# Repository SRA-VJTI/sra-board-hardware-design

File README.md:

<!-- PROJECT LOGO -->

[![Stargazers][stars-shield]][stars-url]
[![Forks][forks-shield]][forks-url]
[![Issues][issues-shield]][issues-url]
[![License][license-shield]][license-url]

<br/>

<p align="center">

  <h3 align="center">SRA Development Board</h3>
  <p align="center">
    ESP32-based Development Board
    <br />
    <a href="./sra_dev_board_2026">KiCAD</a>
    ·
    <a href="./gerber_sra_dev_board">Gerber</a>
    ·
    <a href="./documentation/images/board_images/front.png">Images</a>
    ·
    <a href="./3d_models/sra_board_model/sra_dev_board_2026.step">3D Model</a>
  </p>

# SRA Board 2026

The SRA board is a development board based on ESP32 with on-board peripherals like a programmable LED matrix, switches, sensor ports for Line Sensor Array and MPU-6050, protection circuit for over-current and reverse voltage, and motor drivers.

## Table of Contents

- [SRA Board 2026](#sra-board-2026)
  - [Table of Contents](#table-of-contents)
  - [Board Images](#board-images)
  - [About the Project](#about-the-project)
  - [Getting Started with a Development Board](#getting-started-with-a-development-board)
  - [Notable problems in the current SRA Board](#notable-problems-in-the-current-sra-board)
  - [Improvements Suggested for Future Iterations](#improvements-suggested-for-future-iterations)
  - [Potential Future Enhancements](#potential-future-enhancements)
  - [3D Models](#3d-models)
  - [Milestones](#milestones)
  - [Contributors](#contributors)
  - [Acknowledgements and Resources](#acknowledgements-and-resources)
  - [License](#license)

## Board Images

- **Frontside**

- **Backside**

## About the Project

- This development board is used for the [Wall-E](https://github.com/SRA-VJTI/Wall-E) and [MARIO](https://github.com/SRA-VJTI/MARIO) workshops conducted by [SRA](https://github.com/SRA-VJTI).
- Designed using KiCAD. The schematic and board files are [here](./sra_dev_board_2026).
- Resources for [previous work](https://github.com/SRA-VJTI/sra-board-hardware-design/tree/v2.5). For more details of the SRA board 2024, checkout this [link](https://github.com/SRA-VJTI/sra-board-hardware-design/releases/tag/v2.4).
- The SRA board 2023 images can be found [here](https://github.com/SRA-VJTI/sra-board-hardware-design/tree/v2.3/documentation/images).
- Older versions of the board and miscellaneous designs can be found [here](https://github.com/SRA-VJTI/PCB-Schematics-and-Layouts).

## Getting Started with a Development Board

In general, every development board has the following basic features:

- ### Power Supply Unit
  - Microcontrollers (MCUs) usually run on 3.3V or 5V logic supply voltage while input to a development board is normally 12V for motor and driving/controlling peripheral devices.
  - So, in order to have a single input source, a _power_ section which inter converts this 12V to standard levels like 5V & 3.3V for MCU and sensors is present.This is achieved using a step-down [buck regulator](https://www.youtube.com/watch?v=m8rK9gU30v4).
  - Buck Regulator IC [MP1584](./datasheets/MP1584_buck.pdf) is used in the current SRA Board 2026 for stepping down the voltage from 12V to 5V DC. This 5V is further regulated to 3.3V using LDO IC [AMS1117-3.3](./datasheets/ams1117_ldo.pdf). The MP1584 is a more compact and efficient alternative compared to the previous LM2576-S.
  - The previous edition of the SRA board (2025) used the [LM2576-S-5](./datasheets/lm2576_buck_regulator.pdf) buck regulator, while earlier editions used the LM7805 linear voltage regulator for stepping down from 12V to 5V.
  - The older editions of the SRA board used the LD33 linear voltage regulator for converting 5V to 3.3V at the sensor port.

- ### Motor Driver
  - Motors usually run on 12V and MCU output is generally 5V/3.3V. So, an external motor driver circuitry is required to control motors according to the MCU input.
  - The current and previous editions of SRA board use the [TB6612FNG](./datasheets/TB6612FNG_motor_driver.pdf) Motor Driver, which is a MOS-based H-Bridge motor driver.
  - The older editions of SRA Board used the L298N IC for motor-control, which is a BJT-based H-Bridge motor driver.

- ### Sensor Port
  - According to the external sensor types, usually development boards have onboard sensor ports where the sensors can be connected easily. [LSA - Line Sensor Array]() and [MPU- Motion Processing Unit]() have on-board connection ports.
  - The current edition uses easily available and efficient [JST XH connectors](https://en.wikipedia.org/wiki/JST_connector).
  - Previous versions used bulky [FRC connectors](<https://www.sunrom.com/c/frc-idc-flat-cable-box-header#:~:text=FRC%20(Flat%20Ribon%20Cable)%20are,from%206%20to%2064%20pins.>)

- ### Protection against [Reverse Voltage](https://www.google.com/url?sa=t&rct=j&q=&esrc=s&source=web&cd=&cad=rja&uact=8&ved=2ahUKEwjc8aaX1c3rAhXXXSsKHXphBgQQFjABegQICxAD&url=https%3A%2F%2Fwww.ti.com%2Flit%2Fpdf%2Fslva139&usg=AOvVaw0Qbub75JJ986MzLv6FYWKE)
  - The SRA Boards use diodes for reverse voltage protection in the power-line.
  - 12V Motor line and power regulated line have been separated with [SS34](./datasheets/ss34_3A_schottky_diode.pdf) and [SS54](./datasheets/ss24_2A_schottky_diode.pdf) schottky diodes respectively.

- ### Protection against [Over Current](https://www.baypower.com/blog/what-is-overcurrent-protection/#:~:text=Overcurrent%20protection%20is%20the%20method,of%20a%20piece%20of%20equipment.)
  - Earlier, for the overcurrent protection of MCU and motor driver circuit, bulky glass fuses of 300mA and 3A were used respectively. After breakdown, they used to be replaced.
  - In the recent versions of the board, these were replaced with compact, PTC Resettable Fuses.
  - On 12V line - [RXEF160](./datasheets/RUEF160_3,2A_trip_ptc_fuse.pdf) : 1.6A hold current; 3.2A trip current Fuse was used.
  - On 5V line - [RXEF160](./datasheets/RXEF050_1A_trip_ptc_fuse.pdf) : 0.5A hold current; 1A trip current Fuse was used.
- ### Programmable Switches and LEDs
  - Every development board should have some programmable switches and LEDs for testing, control and debugging purposes.
  - The current SRA Board 2026 features a 6x5 LED matrix (30 LEDs total) controlled via shift registers, which provides enhanced debugging capabilities and expressive visual feedback while reducing GPIO usage compared to discrete LEDs.
  - The previous edition (2025) had an array of 8 programmable discrete LEDs and switches.
  - The earlier editions had fewer programmable switches and LEDs for testing and control purposes.

- ### Power Switch
  - All versions have a power switch for the motor driver, using which power supply to the motor driver can be toggled. Similarly, there was a switch for the ESP32 MCU.

> Now that we covered basics of development boards, let us talk about the changes made in the new design.

## Changes IN SRA Board Over the years from 2024-2026

|            Feature            |           SRA Board 2024           |           SRA Board 2025           |            SRA Board 2026            |
| :---------------------------: | :--------------------------------: | :--------------------------------: | :----------------------------------: |
|           12V to 5V           |      LM2576-S Buck Converter       |      LM2576-S Buck Converter       |        MP1584 Buck Converter         |
|  Reverse Voltage Protection   |               Diodes               |               Diodes               |                Diodes                |
|   Line Sensing Arrays (LSA)   |             IR Sensors             |             IR Sensors             |              IR Sensors              |
|     Number of LSA Sensors     |                 5                  |                 5                  |                  5                   |
|         Motor Driver          |             TB6612FNG              |             TB6612FNG              |              TB6612FNG               |
|     Stepper Motor Driver      |                 -                  |                 -                  |                  -                   |
|   No. of DC Motor Channels    |                 2                  |                 2                  |                  2                   |
| No. of Stepper Motor Channels |                 0                  |                 0                  |                  0                   |
|        No. of Switches        |                 2                  |                 2                  |                  2                   |
|          No. of LEDs          |                 8                  |                 8                  | 6x5 LED Matrix (via Shift Registers) |
|    Over Current Protection    |        PTC Resettable Fuses        |        PTC Resettable Fuses        |         PTC Resettable Fuses         |
|    Sensor Port Connectors     |           JST Connectors           |           JST Connectors           |            JST Connectors            |
| Component Type and Board Size | SMD(Surface Mount Device), Smaller | SMD(Surface Mount Device), Smaller |  SMD(Surface Mount Device), Smaller  |
|         ESP32 Module          |           Not Integrated           |    Mounted and Soldered to PCB     |     Mounted and Soldered to PCB      |
|         Flashing Port         |             Micro USB              |               Type-C               |                Type-C                |

- ### **Compatiblity of SRA Board with Battery [3- 3.3V 2500mAh Batteries](https://robu.in/product/bak-nmc-18650-2500mah-8c-lithium-ion-battery/?gad_source=1&gclid=Cj0KCQjw6PGxBhCVARIsAIumnWb20iyJUEXE8V6eAfSambP35PfBsSFKje-ALjyNniqGYCW_kz3IbcQaAoeGEALw_wcB)**
  - The SRA Board is compatible with **3-cell (3S) Lithium-ion battery packs** which use an external **[BMS (Battery Management System)](https://robu.in/product/3s-10a-12v-18650-lithium-battery-charger-board-protection-module/)**.
  - The BMS helps maintain safe operating voltages and disconnects the battery when the voltage drops below a safe limit.
  - It also ensures balanced charging and discharging of the three cells, improving the overall health and lifetime of the battery pack.

- ### **7805 (5V linear regulator) to [LM2576/96 Buck Convertor](https://www.youtube.com/watch?v=m8rK9gU30v4)**
  - The higher efficiency, output current capability and reliability of LM2576/96 were the primary reasons for this change.
  - The efficiency of LM2576 can reach up to **~92%**, which is significantly better than the 7805 linear regulator.
  - The LM2576 can provide currents up to **3A**, allowing peripherals such as the MARIO workshop manipulator to be powered using the onboard regulator.

- ### **LD33 (3.3V) to [AMS1117](http://www.advanced-monolithic.com/pdf/ams1117.pdf)**:
  - Older editions used the **LD33 IC** to step down from 5V to 3.3V.
  - This was later replaced with the **AMS1117-3.3 LDO**, which is more compact and widely used for stable 3.3V regulation.
  - (_AMS1117 is also used on the ESP32-DevKitC V4 module._)

- ### **Reverse voltage protection: Diodes to P-MOSFET**
  - Diodes placed in series with the power line introduce voltage drop and power loss compared to a **P-MOSFET based protection circuit**.
  - Due to the higher current requirements of the motors, managing diode size and current rating became difficult.
  - Therefore, earlier versions used a **P-MOSFET based reverse polarity protection circuit**, which is more efficient and can handle higher currents.
  - In the current edition, **SMD Schottky diodes** are used, making size and rating less of an issue.

- ### **Component Type and Board Size**:
  - In the previous editions, THT/PTH (Through-Hole) components were used, which occupied more board area and increased in size with higher power ratings.
  - In the current edition, the design adopts a more compact SMD-based layout. The LM2576 buck converter has been replaced with the smaller MP1584 regulator, and the discrete LED array has been replaced with a 6×5 LED matrix driven using shift registers.
  - Current Board Dimensions: **90mm x 90mm**

- ### **L298N vs [TB6612FNG](https://dronebotworkshop.com/tb6612fng-h-bridge/)**
  - L298N is a BJT-based H-bridge motor driver but it is less efficient as compared to the new MOS-based TB6612FNG.
  - The detailed comparison is shown below. As you can see the efficiency of TB6612FNG can reach up to 91-95% which is significantly higher than the 40-70% efficiency of L298N.
  - The only drawback of TB6612FNG is the less continuous current which is equal to 1.2A.

- ### **LED System**

  - Earlier versions of the board used a set of discrete programmable LEDs for debugging and status indication. In the SRA Board 2026, this has been replaced with a **6×5 LED matrix driven using shift registers**.  
  - This significantly reduces GPIO usage while allowing more flexible visual debugging and status indication patterns.

## Notable problems in the current SRA Board

- ### **Buck Converter Stability Issue (MP1584)**
  - The SRA Board 2026 uses the **MP1584 buck converter** to step down 12V to 5V.
  - While the device allowed a significant reduction in the power section size compared to LM2576, irregular behaviour was observed under **higher load conditions**.
  - During heavy load scenarios involving motors and other peripherals, the **5V rail occasionally showed instability**, which may affect the overall system reliability.

- ### **USB Type-C Connector Mechanical Strength Issue**
  - The board currently uses a **16-pin USB Type-C connector** for programming and power.
  - In practical usage, the connector was found to be **mechanically weak**, and in some cases it could loosen or detach from the PCB after repeated cable insertion or mechanical stress.

- ### **Power Switch Issue**
  - There are two dpdt power toggle switch used on board. One to toggle the supply of 12v to the whole board and one to toggle the supply of 5v to the logic circuit.
  - Instead it should have been toggling 12v supply to the motors and toggling 12v supply to the whole board.

## Improvements Suggested for Future Iterations

Based on the current design of the SRA Board 2026, the following improvements are recommended for future iterations:

- **Replace MP1584 with TPS562202**: The TPS562202 offers improved reliability and enhanced long-term robustness compared to the current MP1584 buck converter. This component provides better thermal performance and more stable regulation across varying load conditions.

- **Upgrade to USB-C 6P Connector**: Replace the current Type-C connector with a robust USB-C 6P connector configuration. This simplifies soldering procedures, improves mechanical strength, and enhances durability during repeated connection cycles.

- **Add Unconnected UART Solder Pads (RX, TX)**: Incorporate unconnected solder pads for UART receive and transmit lines on the PCB. This allows the board to optionally function as a USB-to-TTL interface, extending its utility beyond standalone development applications.

## Potential Future Enhancements

The following experimental features and enhancements are being considered for future versions of the SRA Board but are not yet integrated into the 2026 iteration:

- **Onboard IMU Integration**: Direct integration of an Inertial Measurement Unit (IMU) for advanced motion sensing applications, eliminating the need for external MPU6050 connections.

- **Camera FFC/FPC Connector**: Addition of a Flat Flex Cable (FFC) or Flexible Printed Circuit (FPC) connector to support camera modules, enabling vision-based robotics projects and computer vision applications.

- **Integrated Motor Driver**: Direct onboarding of motor driver circuits instead of requiring external TB6612FNG modules, reducing component count and improving form factor.

- **CH340 to CP2102 Upgrade**: Replacing the CH340 USB-to-UART bridge with CP2102 for improved reliability, driver support across multiple operating systems, and better stability in industrial environments.

These enhancements represent opportunities for evolution of the platform and will be explored as future iterations of the board are developed.

## 3D Models

1. The complete 3D model (.step) file of [SRA Board 2026](./3d_models/sra_board_model/sra_dev_board_2026.step)
2. The 3D models of motor driver, LEDs, ESP32 etc.: [3d models of other components](./3d_models/)

<!-- Milestone -->

## Milestones

- [x] Designing of the prototype board
- [x] Modular testing of the circuit
- [x] Testing of prototype board
- [x] Final version
- [x] Making the board Battery Compatible
- [x] Onboard ESP32 Module

<!-- CONTRIBUTORS -->

## Contributors

- [Vishal Mutha](https://github.com/Vishal-Mutha): _Designer_
- [Atharva Atre](https://github.com/AtharvaAtre): _Mentor_
<!-- ACKNOWLEDGEMENTS AND REFERENCES -->

## Acknowledgements and Resources

- Previous Edition: [SRA Board 2025](https://github.com/SRA-VJTI/sra-board-hardware-design/releases/tag/v2.5)
- [KiCAD Tutorials](https://www.youtube.com/playlist?list=PL3bNyZYHcRSUhUXUt51W6nKvxx2ORvUQB)
- [README Template](https://github.com/roshanlam/ReadMeTemplate) by [roshanlam](https://github.com/roshanlam)

## License

- Distributed under the [MIT License](https://github.com/SRA-VJTI/sraboard-hardware-design/blob/master/LICENSE).

[forks-shield]: https://img.shields.io/github/forks/SRA-VJTI/sra-board-hardware-design
[forks-url]: https://github.com/SRA-VJTI/sra-board-hardware-design/network/members
[stars-shield]: https://img.shields.io/github/stars/SRA-VJTI/sra-board-hardware-design
[stars-url]: https://github.com/SRA-VJTI/sra-board-hardware-design/stargazers
[issues-shield]: https://img.shields.io/github/issues/SRA-VJTI/sra-board-hardware-design
[issues-url]: https://github.com/SRA-VJTI/sra-board-hardware-design/issues
[license-shield]: https://img.shields.io/github/license/SRA-VJTI/sra-board-hardware-design
[license-url]: https://github.com/SRA-VJTI/sra-board-hardware-design/blob/master/LICENSE

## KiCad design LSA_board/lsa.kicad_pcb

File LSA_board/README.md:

## LSA - Line Sensor Array

### Table of Contents
* [Overview](#overview)
* [Features](#features)
* [Components of LSA](#components-of-lsa)
* [Function of Components](#function-of-components)
	* [LED](#function-of-components)
	* [PhotoDiode](#function-of-components)
	* [IC LM324](#function-of-components)
	* [Resistors](#function-of-components)
* [Connections](#connections)
* [Working Principle](#working-principle)
* [Appplications](#applications)
* [Scope of Improvement](#scope-of-improvement)

### Overview
- The Line Sensor Array(LSA) is used to detect the white/black lined surface and it sends this data to the microcontroller ESP-32. Analyzing and processing the data received by the microcontroller ESP-32, the purpose of line following is achieved.

- Physical PCB

- PCB Backside

### Features
* Components used are readily available.
* Easy connections for output signals.
* Compact enough to fit into any project.
* Distinguished trace widths for Signal and Power Routes.

### Components of LSA
| Component   | Description   | Quantity |
| ----------- | ------------- | -------- |
| Infrared Emmitter         | Emits infrared light   |  5       |
| PhotoTransistor  | Absorbs light |  5       |
| Resistors   | Limit Current |  10      |
|JST Connector | Connect PCB with other circuits|1|

### Function of Components
- **Infrared Emmitter**
	- The specific Infrared Emmitter emit infrared light which is incident on the surface and some of it is absorbed by the surface. The voltage source for the Infrared Emmitter to emit is VCC.

- **PhotoTransistor**
	- Based upon the reflectivity coefficient of the surface( generally less than 1), the remaining light reflected from the surface is captured by the Photodiodes. Infrared Emmitter and complimentary phototransistor are used to efficiently detect the surface (white/black line). The amount of light received is directly proportional to the current generated by it. More the light, more the current, more the reading.

- **Resistors**
	- Now to limit the current and thus to protect the LEDs, PhotoDiodes current limiting resistors are used.

### Connections
To connect LSA with the SRA Board, connect the JST connector in the following way:

### Working Principle
- LSA works on the principle of reflectivity of light for different types of surfaces.
	- Black Surface -> HIGH absorptivity -> LESS reflectivity
	- White Surface -> LOW absorptivity -> HIGH reflectivity
- Demonstration

### Applications
* Obstacle detection on a clear path.
* Line Following.
* Distinguish Colours on a path.

### Scope of Improvement
- LSA sometimes provides slightly inaccurate readings due to external light and conditions due to non uniformity of the colour of the path. Therefore, LSA has low accuracy. Hence LSA should be kept close to the ground.
- As of now only white and black surfaces are being mapped. Given accurate sensors and proper mapping we can map LSA for any range of RGB colours.

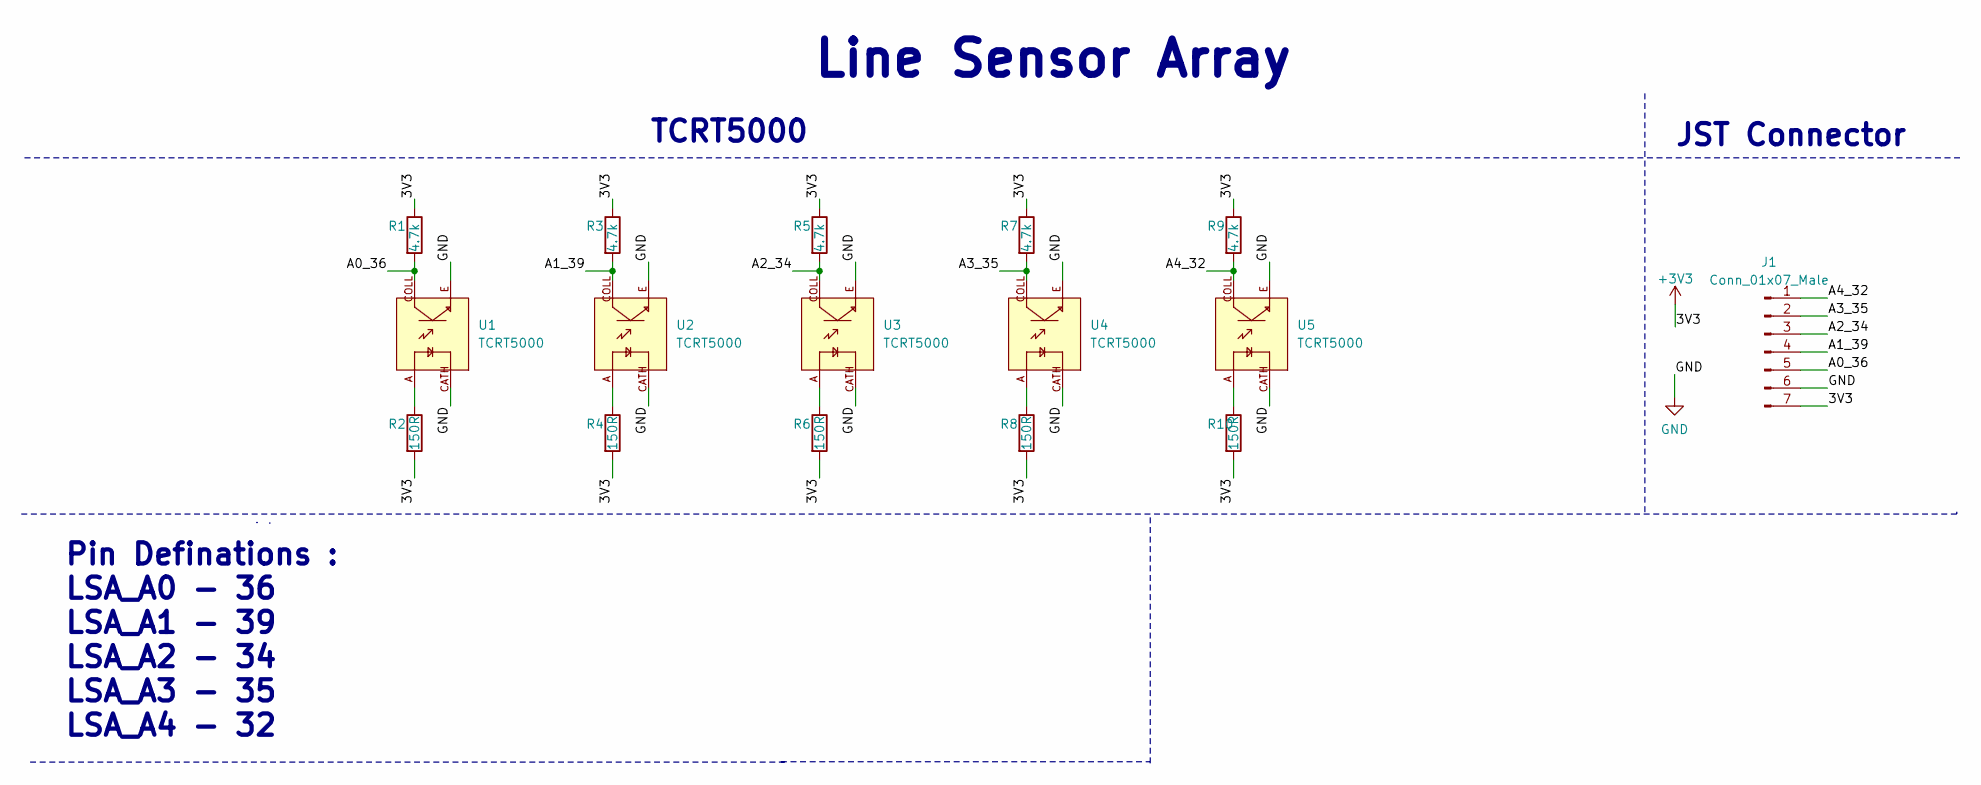
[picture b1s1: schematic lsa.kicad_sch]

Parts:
J1: Conn_01x07_Male; PinHeader_1x07_P2.54mm_Vertical
R1, R3, R5, R7, R9: 4.7k; R_1206_3216Metric_Pad1.30x1.75mm_HandSolder
R2, R4, R6, R8, R10: 150R; R_1206_3216Metric_Pad1.30x1.75mm_HandSolder
U1, U2, U3, U4, U5: TCRT5000; OPTO_TCRT5000; PARTREV 1.7

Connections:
+3V3: J1.7, R1.1, R2.2, R3.1, R4.2, R5.1, R6.2, R7.1, R8.2, R9.1, R10.2
/A0_36: J1.5, R1.2, U1.COLL
/A1_39: J1.4, R3.2, U2.COLL
/A2_34: J1.3, R5.2, U3.COLL
/A3_35: J1.2, R7.2, U4.COLL
/A4_32: J1.1, R9.2, U5.COLL
GND: J1.6, U1.CATH, U1.E, U2.CATH, U2.E, U3.CATH, U3.E, U4.CATH, U4.E, U5.CATH, U5.E
unnamed: R2.1, U1.A
unnamed: R4.1, U2.A
unnamed: R6.1, U3.A
unnamed: R8.1, U4.A
unnamed: R10.1, U5.A

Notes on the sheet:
JST Connector
Line Sensor Array
TCRT5000
Pin Definations : LSA_A0 - 36 LSA_A1 - 39 LSA_A2 - 34 LSA_A3 - 35 LSA_A4 - 32

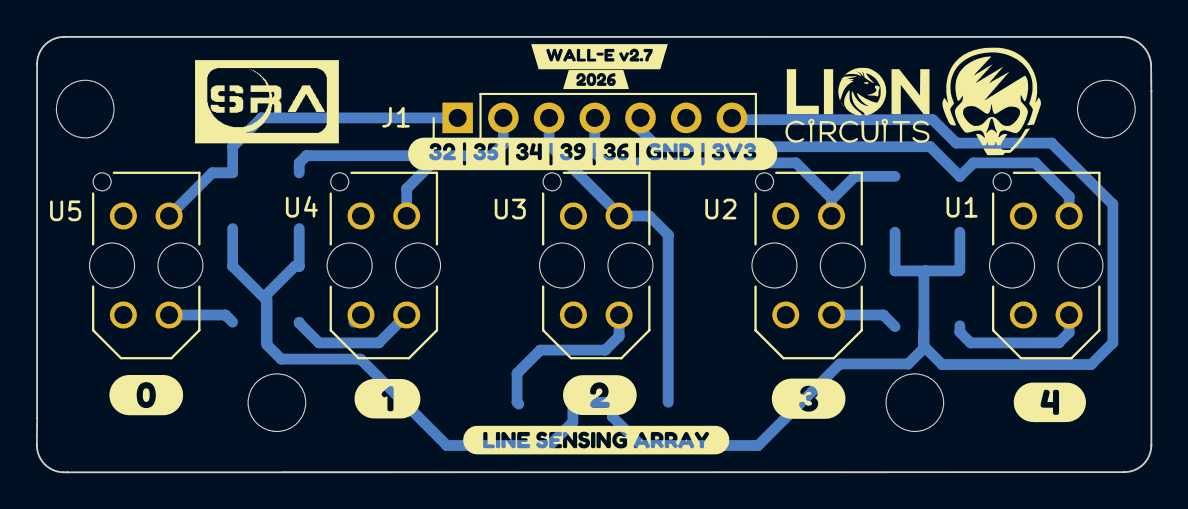
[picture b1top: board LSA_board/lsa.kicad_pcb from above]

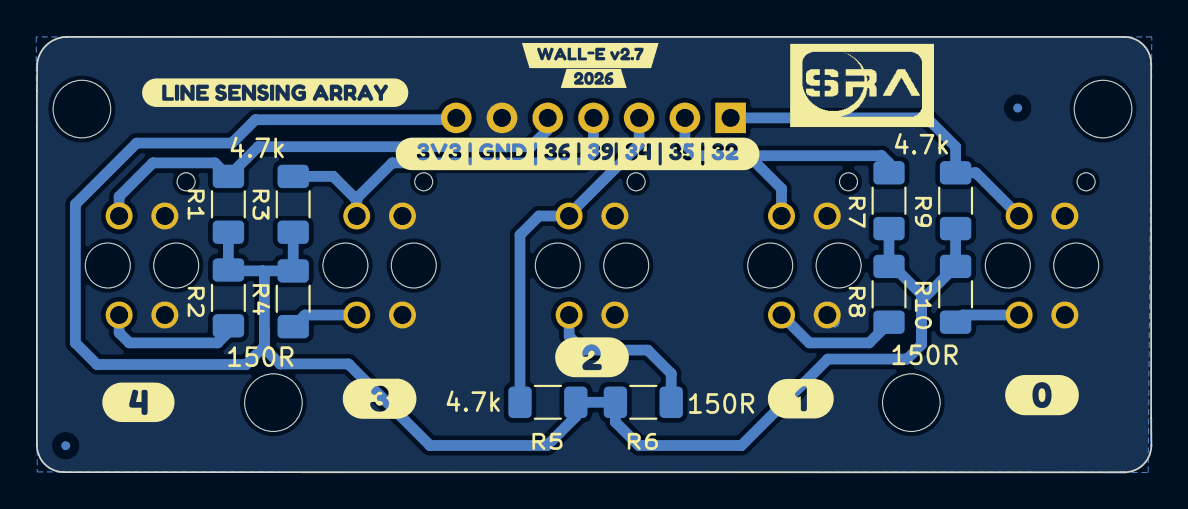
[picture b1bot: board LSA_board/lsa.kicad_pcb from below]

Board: 2 copper layers, 61.9 x 24.2 mm, 34 parts (19 on the bottom side), 12 nets.

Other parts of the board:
kibuzzard-68E92CD3, kibuzzard-68E92CD3#2: G***; kibuzzard-68E92CD3
kibuzzard-68E92CE3, kibuzzard-68E92CE3#2: G***; kibuzzard-68E92CE3
kibuzzard-672CF9E4, kibuzzard-672CF9E4#2: G***; kibuzzard-672CF9E4
kibuzzard-6394EC2D: G***; kibuzzard-6394EC2D
kibuzzard-63708C00: G***; kibuzzard-63708C00
kibuzzard-63708D58, kibuzzard-63708D58#2: G***; kibuzzard-63708D58
kibuzzard-63708D75, kibuzzard-63708D75#2: G***; kibuzzard-63708D75
kibuzzard-63708D85, kibuzzard-63708D85#2: G***; kibuzzard-63708D85
kibuzzard-63708DAF, kibuzzard-63708DAF#2: G***; kibuzzard-63708DAF
kibuzzard-63708DBF, kibuzzard-63708DBF#2: G***; kibuzzard-63708DBF

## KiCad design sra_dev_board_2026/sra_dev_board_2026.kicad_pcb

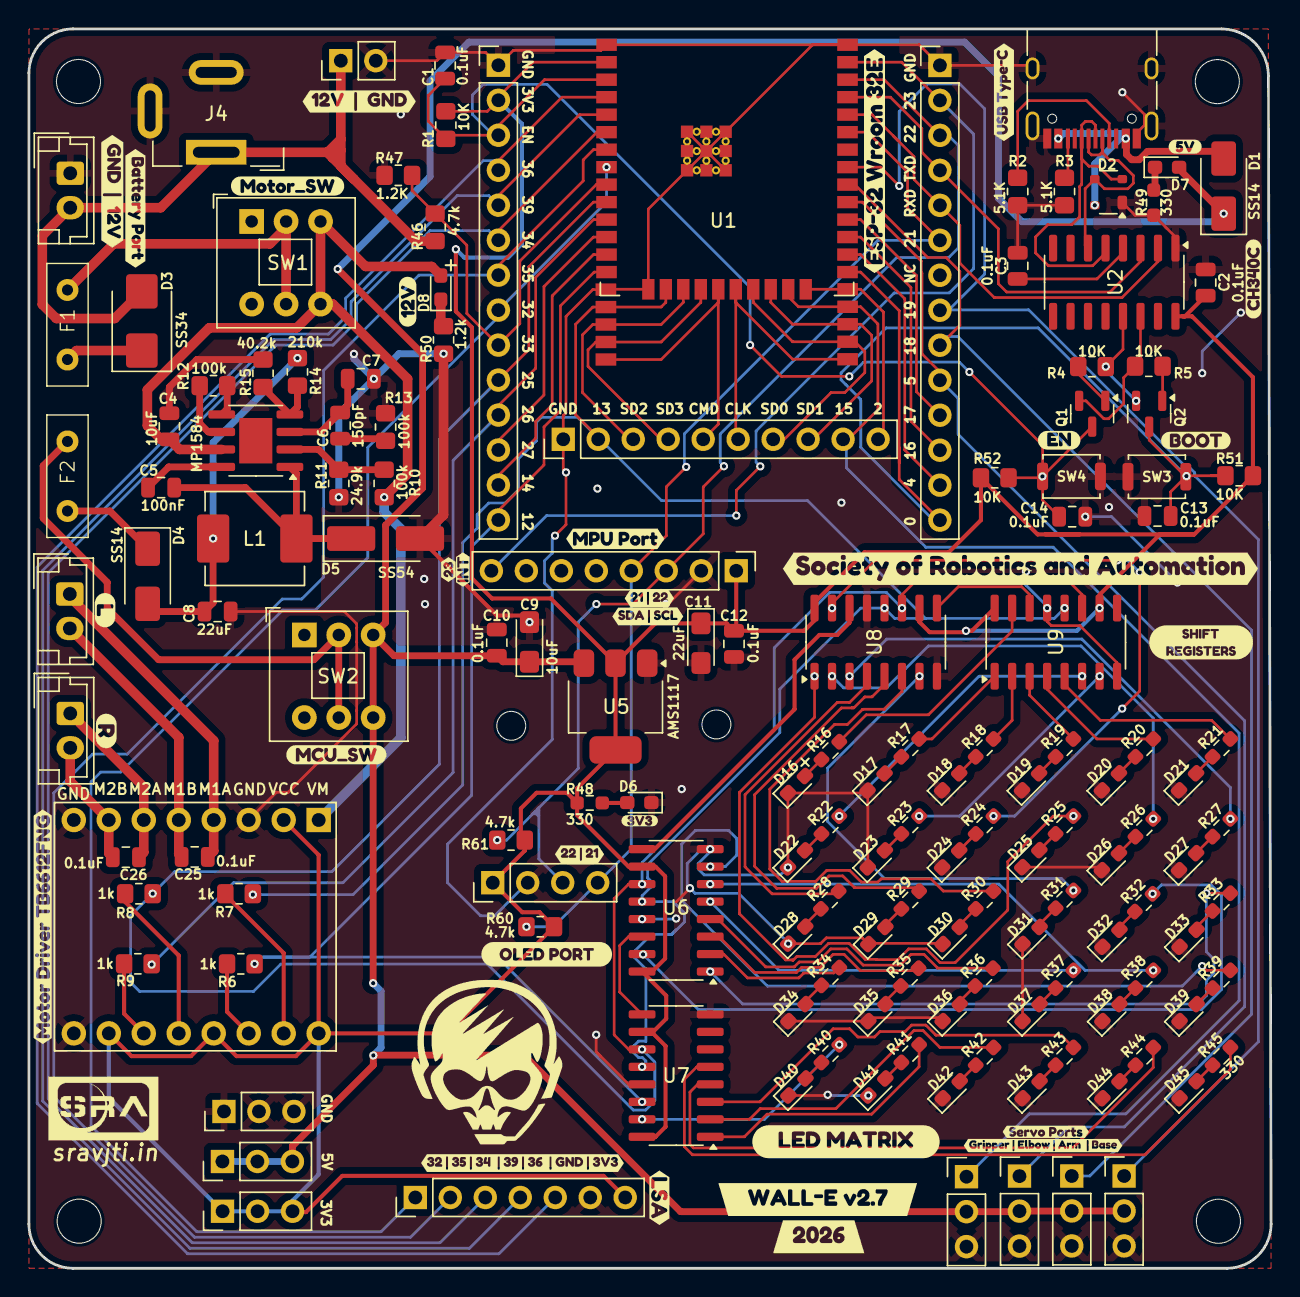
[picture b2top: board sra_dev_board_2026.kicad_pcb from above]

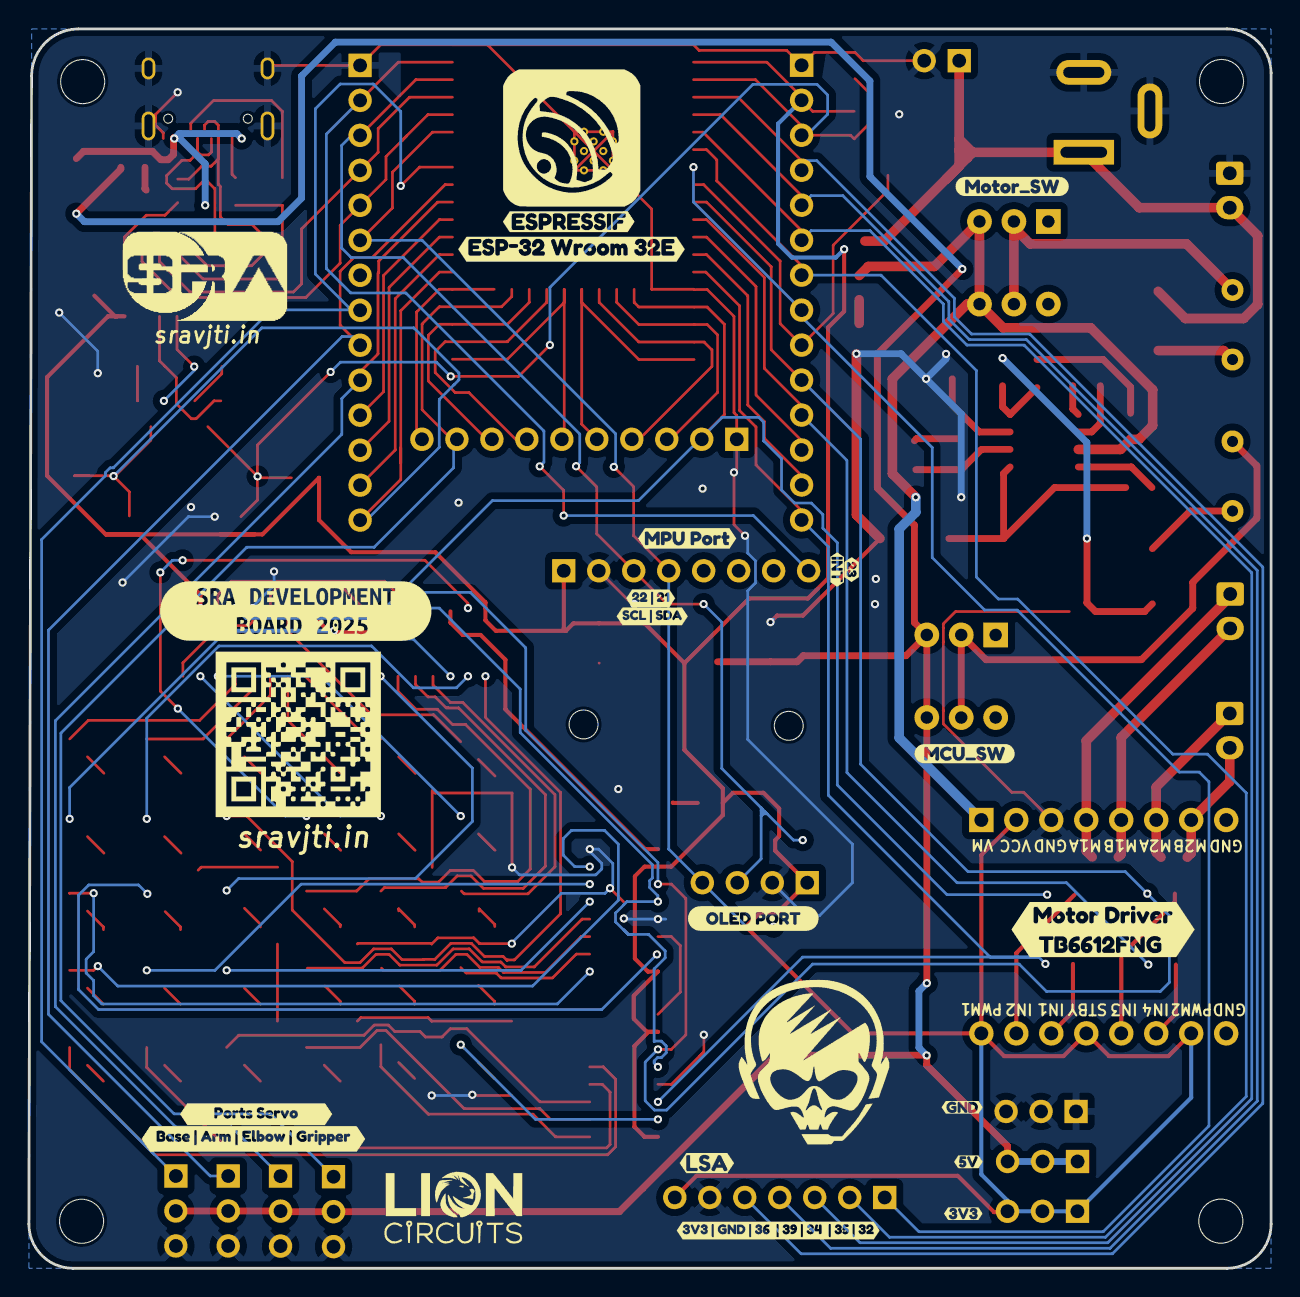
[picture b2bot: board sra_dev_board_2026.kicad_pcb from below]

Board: 2 copper layers, 90.2 x 90.0 mm, 202 parts (19 on the bottom side), 134 nets.

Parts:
C1, C2, C3, C10, C12, C13, C14, C25, C26: 0.1uF; C_0805_2012Metric
C4: 10uF; C_0805_2012Metric
C5: 100nF; C_0805_2012Metric
C6: 150pF; C_0805_2012Metric
C7: NS; C_0805_2012Metric
C8: 22uF; C_0805_2012Metric
C9: 10uF; CP_EIA-3216-10_Kemet-I_HandSolder
C11: 22uF; CP_EIA-3216-10_Kemet-I_HandSolder
D1, D4: SS14; D_SMA
D2: SP0503BAHT; SOT-143
D3: SS34; D_SMB
D5: D_Schottky; D_SMA_Handsoldering
D6, D7, D8, D16, D17, D18, D19, D20, D21, D22, D23, D24, D25, D26, D27, D28, D29, D30, D31, D32, D33, D34, D35, D36, D37, D38, D39, D40, D41, D42, D43, D44, D45: LED; LED_0603_1608Metric_Pad1.05x0.95mm_HandSolder
F1: 3A; Fuse_Littelfuse-LVR100
F2: 1A; Fuse_Littelfuse-LVR100
H1, H2, H3, H4: MountingHole; MountingHole_3.2mm_M3
H5, H6: MountingHole; MountingHole_2.1mm
J1: USB_C_Receptacle_USB2.0_16P; USB_C_Receptacle_GCT_USB4105-xx-A_16P_TopMnt_Horizontal
J2, J3, J6: B2B-XH-A_LF__SN_; JST_EH_B2B-EH-A_1x02_P2.50mm_Vertical
J4: Barrel_Jack_Switch; BarrelJack_Wuerth_6941xx301002
J5: Screw_Terminal_01x02; PinHeader_1x02_P2.54mm_Vertical
J7, J8, J9, J10: Conn_01x03_Male; PinHeader_1x03_P2.54mm_Vertical
J11: Conn_01x08_Female; PinHeader_1x08_P2.54mm_Vertical
J12: Conn_01x04_Female; PinHeader_1x04_P2.54mm_Vertical
J13: Conn_01x07_JST; PinHeader_1x07_P2.54mm_Vertical
J14, J15: Conn_01x14; PinHeader_1x14_P2.54mm_Vertical
J16: Conn_01x10; PinHeader_1x10_P2.54mm_Vertical
J20, J21, J22: Conn_01x03_Pin; PinHeader_1x03_P2.54mm_Vertical
L1: 15uH; L_Sunlord_MWSA0603S
Q1, Q2: SS8050; SOT-23
R1, R4, R5, R51, R52: 10K; R_0805_2012Metric_Pad1.20x1.40mm_HandSolder
R2, R3: 5.1K; R_0805_2012Metric_Pad1.20x1.40mm_HandSolder
R6, R7, R8, R9: 1k; R_0805_2012Metric_Pad1.20x1.40mm_HandSolder
R10, R12, R13: 100k; R_0805_2012Metric_Pad1.20x1.40mm_HandSolder
R11: 24.9k; R_0805_2012Metric_Pad1.20x1.40mm_HandSolder
R14: 210k; R_0805_2012Metric_Pad1.20x1.40mm_HandSolder
R15: 40.2k; R_0805_2012Metric_Pad1.20x1.40mm_HandSolder
R16, R17, R18, R19, R20, R21, R22, R23, R24, R25, R26, R27, R28, R29, R30, R31, R32, R33, R34, R35, R36, R37, R38, R39, R40, R41, R42, R43, R44, R45, R48, R49: 330; R_0603_1608Metric_Pad0.98x0.95mm_HandSolder
R46, R60, R61: 4.7k; R_0805_2012Metric_Pad1.20x1.40mm_HandSolder
R47: 1.2K; R_0805_2012Metric_Pad1.20x1.40mm_HandSolder
R50: 1.2k; R_0805_2012Metric_Pad1.20x1.40mm_HandSolder
SW1, SW2: SW_Push_DPDT; SW_Push_2P2T_Toggle_CK_PVA2OAH5xxxxxxV2
SW3: SW_0; SW_Push_SPST_NO_Alps_SKRK
SW4: SW_EN; SW_Push_SPST_NO_Alps_SKRK
U1: ESP32-WROOM-32E
U2: CH340C; SOIC-16_3.9x9.9mm_P1.27mm
U3: TB6612FNG H-bridge Motor Driver; TB6612FNG
U4: MP1584; SOIC-8-1EP_3.9x4.9mm_P1.27mm_EP2.41x3.3mm
U5: AMS1117-3.3; SOT-223-3_TabPin2
U6, U7, U8, U9: 74HC595; SOIC-16_3.9x9.9mm_P1.27mm
kibuzzard-66CD8CDE: G***; kibuzzard-66CD8CDE
kibuzzard-66CD901B: G***; kibuzzard-66CD901B
kibuzzard-66CF86D1, kibuzzard-66CF86D1#2: G***; kibuzzard-66CF86D1
kibuzzard-66CF86E5, kibuzzard-66CF86E5#2: G***; kibuzzard-66CF86E5
kibuzzard-66D06F4C: G***; kibuzzard-66D06F4C
kibuzzard-66D06F54: G***; kibuzzard-66D06F54
kibuzzard-66D06403: G***; kibuzzard-66D06403
kibuzzard-66D58886: G***; kibuzzard-66D58886
kibuzzard-67A02922: G***; kibuzzard-67A02922
kibuzzard-68E7F7FE: G***; kibuzzard-68E7F7FE
kibuzzard-68E7F8BB: G***; kibuzzard-68E7F8BB
kibuzzard-68E7F8DA: G***; kibuzzard-68E7F8DA
kibuzzard-68E7F82B: G***; kibuzzard-68E7F82B
kibuzzard-68E7F907: G***; kibuzzard-68E7F907
kibuzzard-68F853B4: G***; kibuzzard-68F853B4
kibuzzard-68F85563: G***; kibuzzard-68F85563
kibuzzard-68F85801: G***; kibuzzard-68F85801
kibuzzard-658F2C3C, kibuzzard-658F2C3C#2: G***; kibuzzard-658F2C3C
kibuzzard-658F2C13, kibuzzard-658F2C13#2: G***; kibuzzard-658F2C13
kibuzzard-668D4F46, kibuzzard-668D4F46#2: G***; kibuzzard-668D4F46
kibuzzard-668D4F81, kibuzzard-668D4F81#2: G***; kibuzzard-668D4F81
kibuzzard-668FE423: G***; kibuzzard-668FE423
kibuzzard-668FF9B2, kibuzzard-668FF9B2#2: G***; kibuzzard-668FF9B2
kibuzzard-675FD791: G***; kibuzzard-675FD791
kibuzzard-675FDA6A: G***; kibuzzard-675FDA6A
kibuzzard-675FE5A8: G***; kibuzzard-675FE5A8
kibuzzard-675FE5B2: G***; kibuzzard-675FE5B2
kibuzzard-675FF2F7: G***; kibuzzard-675FF2F7
kibuzzard-675FF39E: G***; kibuzzard-675FF39E
kibuzzard-6774F3BB: G***; kibuzzard-6774F3BB
kibuzzard-6774F4AA: G***; kibuzzard-6774F4AA
kibuzzard-6774F4AE: G***; kibuzzard-6774F4AE
kibuzzard-66914CE9: G***; kibuzzard-66914CE9
kibuzzard-67602C35: G***; kibuzzard-67602C35
kibuzzard-67602E60: G***; kibuzzard-67602E60
kibuzzard-67602E69: G***; kibuzzard-67602E69
kibuzzard-67704C04: G***; kibuzzard-67704C04
kibuzzard-67704CCE: G***; kibuzzard-67704CCE
kibuzzard-67704CDF: G***; kibuzzard-67704CDF
kibuzzard-67704CF4: G***; kibuzzard-67704CF4
kibuzzard-67715A02: G***; kibuzzard-67715A02
kibuzzard-677158DD: G***; kibuzzard-677158DD
kibuzzard-66921043: G***; kibuzzard-66921043
kibuzzard-66923428: G***; kibuzzard-66923428

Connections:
/0: C13.2, J15.14, Q2.3, R51.1, SW3.2, U1.25 (IO0)
/2: J16.10, U1.24 (IO2)
/3V3: C2.1, C11.1, C12.1, J11.1, J12.1, J13.7, J14.2, J22.1, J22.2, J22.3, R1.2, R48.2, R51.2, R52.2, R60.1, R61.1, U1.2 (VDD), U2.16 (VCC), U3.2 (VCC), U3.10 (PWMB), U3.13 (STBY), U3.16 (PWMA), U5.2 (VO), U6.10 (~SRCLR), U6.16 (VCC), U7.10 (~SRCLR), U7.16 (VCC), U8.10 (~SRCLR), U8.16 (VCC), U9.10 (~SRCLR), U9.16 (VCC)
/4: J15.13, U1.26 (IO4)
/5: J8.1, J15.10, U1.29 (IO5)
/5V: C8.1, D4.2 (A), L1.2, R14.1
/5V_P: C9.1, C10.1, D1.1 (K), D7.2 (A), J7.2, J8.2, J9.2, J10.2, J21.1, J21.2, J21.3, SW2.3 (C), SW2.6 (C), U5.3 (VI)
/12: J14.14, R6.1, U1.14 (IO12), U7.14 (SER)
/12V: D3.2 (A), J4.1, J5.1, J6.2, R46.1
/12V_P: C4.1, D8.2 (A), R10.1, SW1.3 (C), SW1.6 (C), U3.1 (VM), U4.7 (VIN)
/13: J16.2, R7.1, U1.16 (IO13), U6.12 (RCLK), U7.12 (RCLK), U8.12 (RCLK), U9.12 (RCLK)
/14: J14.13, U1.13 (IO14)
/15: J7.1, J16.9, U1.23 (IO15)
/16: J15.12, U1.27 (IO16)
/17: J15.11, U1.28 (IO17)
/18: J9.1, J15.9, U1.30 (IO18)
/19: J10.1, J15.8, U1.31 (IO19)
/21: J11.4, J12.4, J15.6, R60.2, U1.33 (IO21)
/22: J11.3, J12.3, J15.3, R61.2, U1.36 (IO22)
/23: J11.8, J15.2, U1.37 (IO23)
/25: J14.10, R8.1, U1.10 (IO25), U6.11 (SRCLK), U7.11 (SRCLK), U8.11 (SRCLK), U9.11 (SRCLK)
/26: J14.11, R9.1, U1.11 (IO26)
/27: J14.12, U1.12 (IO27)
/32: J13.1, J14.8, U1.8 (IO32)
/33: J14.9, R46.2, R47.2, U1.9 (IO33)
/34: J13.3, J14.6, U1.6 (IO34)
/35: J13.2, J14.7, U1.7 (IO35)
/36: J13.5, J14.4, U1.4 (SENSOR_VP)
/39: J13.4, J14.5, U1.5 (SENSOR_VN)
/CLK: J16.6, U1.20 (NC)
/CMD: J16.5, U1.19 (NC)
/D+: D2.2 (K), J1.A6 (D+), J1.B6 (D+), U2.5 (UD+)
/D-: D2.3 (K), J1.A7 (D-), J1.B7 (D-), U2.6 (UD-)
/EN: C1.1, C14.2, J14.3, Q1.3, R1.1, R52.1, SW4.2, U1.3 (EN)
/EN_SR: R10.2, R11.1, U4.2 (EN)
/FB: R14.2, R15.1, U4.4 (FB)
/M1A: C25.1, J3.1, U3.4 (A01)
/M1B: C25.2, J3.2, U3.5 (A02)
/M2A: C26.1, J2.1, U3.6 (B02)
/M2B: C26.2, J2.2, U3.7 (B01)
/RXD: J15.5, U1.34 (RXD0/IO3), U2.2 (TXD)
/SD0: J16.7, U1.21 (NC)
/SD1: J16.8, U1.22 (NC)
/SD2: J16.3, U1.17 (NC)
/SD3: J16.4, U1.18 (NC)
/TXD: J15.4, U1.35 (TXD0/IO1), U2.3 (RXD)
/VBUS: D1.2 (A), D2.4 (K), J1.A4 (VBUS), J1.A9 (VBUS), J1.B4 (VBUS), J1.B9 (VBUS)
/lm1: R16.2, U9.15 (QA)
/lm2: R17.2, U9.1 (QB)
/lm3: R18.2, U9.2 (QC)
/lm4: R19.2, U9.3 (QD)
/lm5: R20.2, U9.4 (QE)
/lm6: R21.2, U9.5 (QF)
/lm7: R22.2, U9.6 (QG)
/lm8: R23.2, U9.7 (QH)
/lm9: R24.2, U8.15 (QA)
/lm10: R25.2, U8.1 (QB)
/lm11: R26.2, U8.2 (QC)
/lm12: R27.2, U8.3 (QD)
/lm13: R28.2, U8.4 (QE)
/lm14: R29.2, U8.5 (QF)
/lm15: R30.2, U8.6 (QG)
/lm16: R31.2, U8.7 (QH)
/lm17: R32.2, U6.15 (QA)
/lm18: R33.2, U6.1 (QB)
/lm19: R34.2, U6.2 (QC)
/lm20: R35.2, U6.3 (QD)
/lm21: R36.2, U6.4 (QE)
/lm22: R37.2, U6.5 (QF)
/lm23: R38.2, U6.6 (QG)
/lm24: R39.2, U6.7 (QH)
/lm25: R40.2, U7.15 (QA)
/lm26: R41.2, U7.1 (QB)
/lm27: R42.2, U7.2 (QC)
/lm28: R43.2, U7.3 (QD)
/lm29: R44.2, U7.4 (QE)
/lm30: R45.2, U7.5 (QF)
/sr2: U6.14 (SER), U7.9 (QH')
/sr3: U6.9 (QH'), U8.14 (SER)
/sr4: U8.9 (QH'), U9.14 (SER)
/~DTR: Q2.2, R4.1, U2.13 (~DTR)
/~RTS: Q1.2, R5.1, U2.14 (~RTS)
GND: C1.2, C2.2, C3.2, C4.2, C7.2, C8.2, C9.2, C10.2, C11.2, C12.2, C13.1, C14.1, D2.1 (A), D5.2 (A), D6.1 (K), D16.1 (K), D17.1 (K), D18.1 (K), D19.1 (K), D20.1 (K), D21.1 (K), D22.1 (K), D23.1 (K), D24.1 (K), D25.1 (K), D26.1 (K), D27.1 (K), D28.1 (K), D29.1 (K), D30.1 (K), D31.1 (K), D32.1 (K), D33.1 (K), D34.1 (K), D35.1 (K), D36.1 (K), D37.1 (K), D38.1 (K), D39.1 (K), D40.1 (K), D41.1 (K), D42.1 (K), D43.1 (K), D44.1 (K), D45.1 (K), J1.A1 (GND), J1.A12 (GND), J1.B1 (GND), J1.B12 (GND), J1.S1 (SHIELD), J4.2, J4.3, J5.2, J6.1, J7.3, J8.3, J9.3, J10.3, J11.2, J12.2, J13.6, J14.1, J15.1, J16.1, J20.1, J20.2, J20.3, R2.2, R3.2, R11.2, R12.2, R13.2, R15.2, R47.1, R49.1, R50.1, SW3.1, SW4.1, U1.1 (GND), U1.15 (GND), U1.38 (GND), U1.39 (GND), U2.1 (GND), U3.3 (GND), U3.8 (GND), U3.9 (GND), U4.5 (GND), U5.1 (GND), U6.8 (GND), U6.13 (~OE), U7.8 (GND), U7.13 (~OE), U8.8 (GND), U8.13 (~OE), U9.8 (GND), U9.13 (~OE)
unnamed: C6.2, R13.1
unnamed: D3.1 (K), F1.1
unnamed: D4.1 (K), F2.1
unnamed: C5.2, D5.1 (K), L1.1, U4.1 (SW)
unnamed: D6.2 (A), R48.1
unnamed: D7.1 (K), R49.2
unnamed: D8.1 (K), R50.2
unnamed: D16.2 (A), R16.1
unnamed: D17.2 (A), R17.1
unnamed: D18.2 (A), R18.1
unnamed: D19.2 (A), R19.1
unnamed: D20.2 (A), R20.1
unnamed: D21.2 (A), R21.1
unnamed: D22.2 (A), R22.1
unnamed: D23.2 (A), R23.1
unnamed: D24.2 (A), R24.1
unnamed: D25.2 (A), R25.1
unnamed: D26.2 (A), R26.1
unnamed: D27.2 (A), R27.1
unnamed: D28.2 (A), R28.1
unnamed: D29.2 (A), R29.1
unnamed: D30.2 (A), R30.1
unnamed: D31.2 (A), R31.1
unnamed: D32.2 (A), R32.1
unnamed: D33.2 (A), R33.1
unnamed: D34.2 (A), R34.1
unnamed: D35.2 (A), R35.1
unnamed: D36.2 (A), R36.1
unnamed: D37.2 (A), R37.1
unnamed: D38.2 (A), R38.1
unnamed: D39.2 (A), R39.1
unnamed: D40.2 (A), R40.1
unnamed: D41.2 (A), R41.1
unnamed: D42.2 (A), R42.1
unnamed: D43.2 (A), R43.1
unnamed: D44.2 (A), R44.1
unnamed: D45.2 (A), R45.1
unnamed: F1.2, SW1.2 (B), SW1.5 (B)
unnamed: F2.2, SW2.2 (B), SW2.5 (B)
unnamed: J1.A5 (CC1), R2.1
unnamed: J1.B5 (CC2), R3.1
unnamed: Q1.1, R4.2
unnamed: Q2.1, R5.2
unnamed: C3.1, U2.4 (V3)
unnamed: R6.2, U3.14 (AI1)
unnamed: R7.2, U3.15 (AI2)
unnamed: R8.2, U3.12 (BI1)
unnamed: R9.2, U3.11 (BI2)
unnamed: C5.1, U4.8 (BST)
unnamed: C6.1, C7.1, U4.3 (COMP)
unnamed: R12.1, U4.6 (FREQ)

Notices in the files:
README.md:
License:
- Distributed under the [MIT License](https://github.com/SRA-VJTI/sraboard-hardware-design/blob/master/LICENSE).
